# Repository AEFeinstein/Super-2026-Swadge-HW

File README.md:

# Super Magfest 2027 Swadge Hardware

## Welcome

This is the hardware repository for the Super Magfest 2027 Swadge.

The corresponding firmware repository for the Super Magfest 2027 Swadge [can be found here](https://github.com/AEFeinstein/Super-2024-Swadge-FW).

If you have any questions, feel free to create a Github ticket or email us at circuitboards@magfest.org.

## Render

Coming eventually!

## Schematic

Coming eventually!

## Directories

### `art`

This directory has the SVGs used to generate the KiCad files. The SVGs are drawn in [Inkscape](https://inkscape.org/).

### `Swadge-Parts`

This directory is a git submodule which has all the parts, footprints, and 3D models used in the KiCad project.

### `Swadge-HW`

This directory has the KiCad project for the main Swadge PCB.

### `Swadge-HW/3d Print`

This directory has the 3D print files for the 2026 Swadge.

### `Swadge-HW/Manufacturing Information`

This directory has information about manufacturing the Swdage PCB.

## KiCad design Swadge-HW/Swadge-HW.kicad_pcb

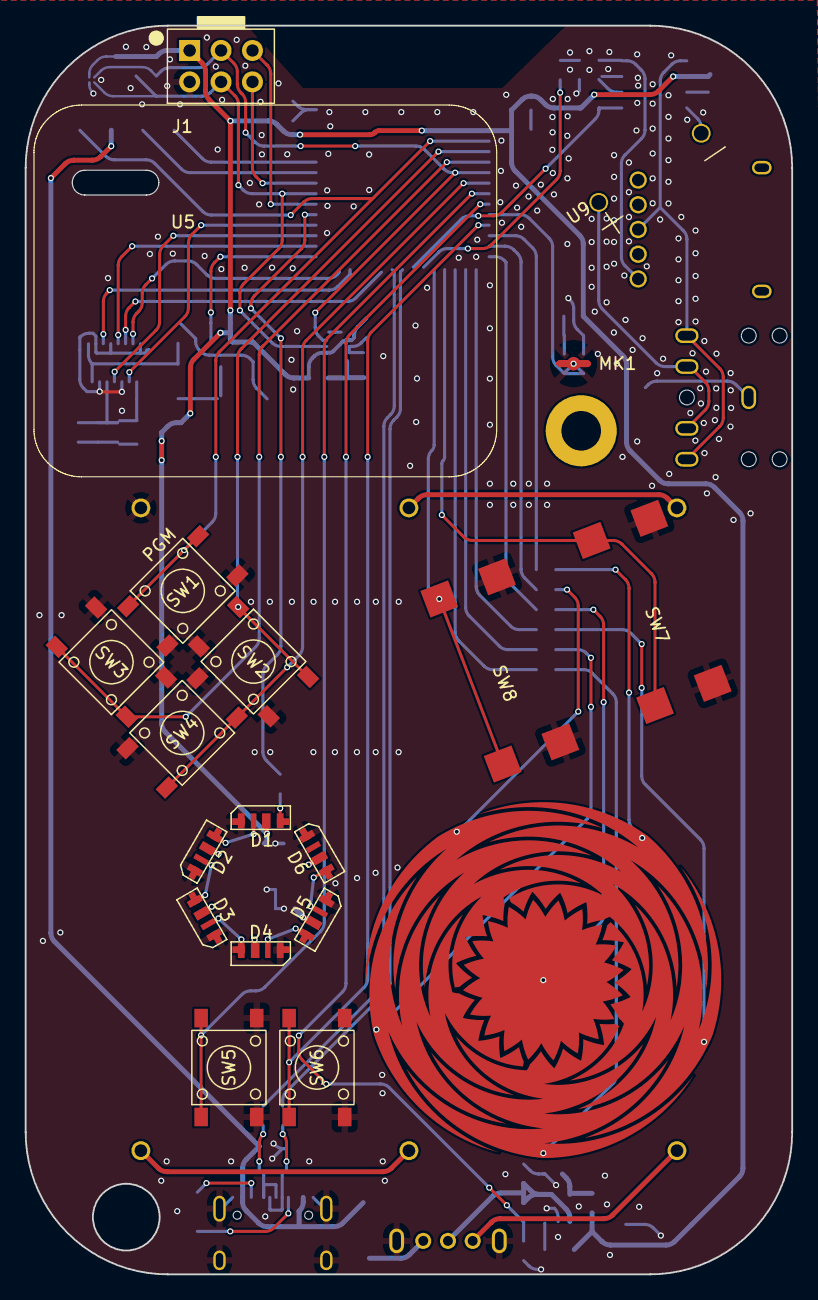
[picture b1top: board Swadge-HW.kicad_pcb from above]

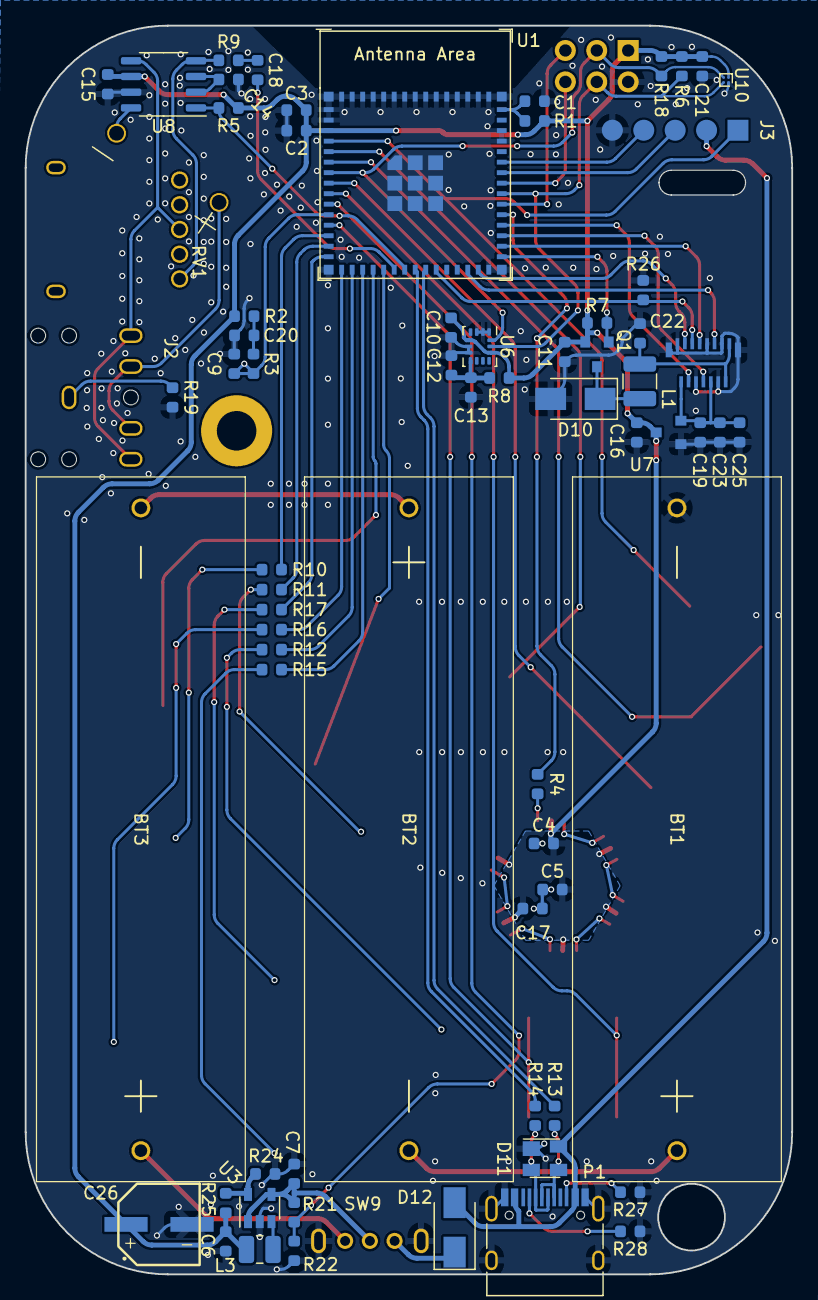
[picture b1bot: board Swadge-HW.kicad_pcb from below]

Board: 2 copper layers, 62.0 x 101.0 mm, 90 parts (70 on the bottom side), 73 nets.

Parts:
BT1, BT2, BT3: Battery; 2460
C1, C4, C5, C6, C7, C11, C14, C15, C17, C19: 1μF; C_0603_1608Metric
C2, C12, C20, C22: 22μF; C_0603_1608Metric
C3, C10, C13, C16, C23, C25: 0.1μF; C_0603_1608Metric
C9: 4.7nF; C_0603_1608Metric
C18: 0.39μF; C_0603_1608Metric
C21: 2.2μF; C_0603_1608Metric
C26: C_Polarized_US; C_Radial_D6.3_L5.8_P5.34
D1, D2, D3, D4, D5, D6: SK6812-SIDE-A; SK6812_SIDE_2
D10, D12: D; D_SMA
D11: SP0503BAHT; SOT-143
J1: Conn_02x03_Odd_Even; PinSocket_2x03_P2.54mm_Vertical
J2: PJ-307C
J3: Conn_01x05_Male; PinHeader_1x05_P2.54mm_Vertical
L1: 33uH_500mA; L_1210_3225Metric
L3: 2.2uH; L_1008_2520Metric
MK1: Microphone; INGHAi_MIC_GMI4013S-2C58DB
P1: USB_C_Plug_USB2.0; USB_C_Receptacle_HRO_TYPE-C-31-M-12
Q1: Q_PMOS_GSD; SOT-23
R1, R7, R22, R24, R26: 10kΩ; R_0603_1608Metric
R2, R4, R8, R13, R14: 33Ω; R_0603_1608Metric
R3: 12kΩ; R_0603_1608Metric
R5, R9: 20kΩ; R_0603_1608Metric
R6, R18, R27, R28: 5.1kΩ; R_0603_1608Metric
R10, R11, R12, R15, R16, R17: 510Ω; R_0603_1608Metric
R19: 120Ω; R_0603_1608Metric
R21, R25: 43kΩ; R_0603_1608Metric
RV1: R_Potentiometer_US_SMD; RK10J11E0034
SW1, SW2, SW3, SW4, SW5, SW6: YTS-D003-1A
SW7, SW8: TS-1103S-B-B; B3FS4002P
SW9: SW_SPDT_1825232-1; 1825232-1
U1: ESP32-S2-MINI-1
U2: RB017A1505A; NULL
U3: M3410; SOT-23-5
U4: Touchpad_6_80
U5: RB017A1505A_Connector; HCTL HC-FPC-03-10-15RLTAG-TUCKED
U6: LSM6DSL; LGA-14_3x2.5mm_P0.5mm_LayoutBorder3x4y
U7: GENERIC_LDO_GOI; SOT-23
U8: FM8002A; SOP-8_3.9x4.9mm_P1.27mm
U9: INGHAi_GSPK2307P-8R1W; INGHAi GSPK2308P-8R0.5W
U10: BGA-4-.83x.83

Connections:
3V3: C2.1, C3.1, C4.1, C5.1, C6.1, C10.1, C11.1, C15.1, C16.1, C17.1, C21.1, C26.1, D1.2 (VDD), D2.2 (VDD), D3.2 (VDD), D4.2 (VDD), D5.2 (VDD), D6.2 (VDD), J1.1, L3.1, Q1.2 (S), R1.1, R2.2, R5.1, R6.2, R7.1, R8.2, R18.1, R25.2, U1.3 (3V3), U6.5 (VDDIO), U6.12 (CS), U7.3 (IN), U8.6 (VDD), U10.B1 (VDD)
5VIN: D11.4 (K), D12.2 (A), J3.2, P1.A4_B9 (VBUS), P1.A9_B4 (VBUS)
+5V: D12.1 (K), SW9.3 (C)
BATTMID: BT1.1 (+), BT2.2 (-)
BATTMID2: BT2.1 (+), BT3.2 (-)
BATTPLUS: BT3.1 (+), SW9.1 (A)
BTN_1: J3.1, SW1.1, SW1.2, U1.4 (GPIO0/BOOT)
BTN_2: SW2.1, SW2.2, U1.5 (GPIO1/ADC1_CH0)
BTN_3: SW3.1, SW3.2, U1.6 (GPIO2/ADC1_CH1)
BTN_4: SW4.1, SW4.2, U1.8 (GPIO4/ADC1_CH3)
BTN_5: SW5.1, SW5.2, U1.9 (GPIO5/ADC1_CH4)
BTN_6: SW6.1, SW6.2, U1.12 (GPIO8/ADC1_CH7)
BTN_7: SW7.1 (COM_1), SW7.2 (COM_2), U1.19 (GPIO15/ADC2_CH4/XTAL_32K_P)
BTN_8: SW8.1 (COM_1), SW8.2 (COM_2), U1.20 (GPIO16/ADC2_CH5/XTAL_32K_N)
CC1: P1.A5 (CC1), R28.2
CC2: P1.B5 (CC2), R27.2
EN: C1.1, R1.2, U1.45 (CHIP/PU/RESET)
GND: BT1.2 (-), C1.2, C2.2, C3.2, C4.2, C5.2, C6.2, C7.2, C9.1, C10.2, C11.2, C12.2, C13.2, C14.1, C15.2, C16.2, C17.2, C19.2, C20.2, C21.2, C22.2, C23.2, C25.2, C26.2, D1.4 (GND), D2.4 (GND), D3.4 (GND), D4.4 (GND), D5.4 (GND), D6.4 (GND), D10.2 (A), D11.1 (A), J1.2, J3.5, MK1.1 (-), P1.A1_B12 (GND), P1.A12_B1 (GND), P1.S1 (SHIELD), R19.1, R22.2, R24.1, R26.2, R27.1, R28.1, SW1.3, SW1.4, SW2.3, SW2.4, SW3.3, SW3.4, SW4.3, SW4.4, SW5.3, SW5.4, SW6.3, SW6.4, SW7.3 (NO_1), SW7.4 (NO_2), SW8.3 (NO_1), SW8.4 (NO_2), SW9.4 (D), SW9.5 (E), U1.1 (GND), U1.2 (GND), U1.30 (GND), U1.42 (GND), U1.43 (GND), U1.46 (GND), U1.47 (GND), U1.48 (GND), U1.49 (GND), U1.50 (GND), U1.51 (GND), U1.52 (GND), U1.53 (GND), U1.54 (GND), U1.55 (GND), U1.56 (GND), U1.57 (GND), U1.58 (GND), U1.59 (GND), U1.60 (GND), U1.61 (GND), U1.62 (GND), U1.63 (GND), U1.64 (GND), U1.65 (GND), U3.2 (GND), U5.1 (GND), U5.6 (GND), U5.9 (GND), U5.12 (LED-), U5.13 (LED-), U5.16 (GND), U5.17 (GND), U6.1 (SA0), U6.2 (SDx), U6.3 (SCx), U6.6 (GND), U6.7 (GND), U7.1 (GND), U8.7 (GND), U10.A1 (VSS)
GPIO40: J1.5, U1.36 (MTDO/JTAG/GPIO40)
GPIO42: J1.6, U1.38 (MTMS/JTAG/GPIO42)
LCD28: C19.1, C23.1, C25.1, U5.2 (VCC1.8V), U5.10 (VDD2.8V), U7.2 (OUT)
LED: R4.2, U1.35 (MTCK/JTAG/GPIO39)
MIC: C9.2, MK1.2 (+), R3.2, U1.11 (GPIO7/ADC1_CH6)
unnamed: C18.1, R9.1
unnamed: C20.1, R2.1, R3.1
unnamed: D1.1 (IN), R4.1
unnamed: D1.3 (OUT), D2.1 (IN)
unnamed: D2.3 (OUT), D3.1 (IN)
unnamed: D3.3 (OUT), D4.1 (IN)
unnamed: D4.3 (OUT), D5.1 (IN)
unnamed: D5.3 (OUT), D6.1 (IN)
unnamed: D10.1 (K), L1.1, Q1.3 (D)
unnamed: J2.1, R19.2
unnamed: D11.2 (K), P1.A7 (DN1), P1.B7 (DN2), R14.2
unnamed: D11.3 (K), P1.A6 (DP1), P1.B6 (DP2), R13.2
unnamed: R24.2, R25.1, U3.5 (FB)
unnamed: L3.2, U3.3 (LX)
unnamed: R10.2, U4.1 (Bottom)
unnamed: R17.2, U4.6 (Center)
unnamed: R16.2, U4.5 (Left)
unnamed: R11.2, U4.2 (Right)
unnamed: R15.2, U4.4 (Top_Left)
unnamed: R12.2, U4.3 (Top_Right)
unnamed: C12.1, C13.1, R8.1, U6.8 (VDD)
unnamed: C14.2, U8.2 (Bypass), U8.3 (IN+)
unnamed: R9.2, RV1.1, U8.4 (IN-)
unnamed: J2.2, J2.5, RV1.2, U8.5 (VO1)
unnamed: U8.8 (VO2), U9.2 (-)
unnamed: J2.3, J2.4, U9.1 (+)
RX: J3.4, U1.40 (GPIO44/U0RXD/PROG)
SCL: J1.4, R6.1, U1.37 (MTDI/JTAG/GPIO41), U6.13 (SCL), U10.A2 (SCL)
SDA: J1.3, R18.2, U1.7 (GPIO3/ADC1_CH2), U6.14 (SDA), U10.B2 (SDA)
SNODE: C7.1, R21.2, SW9.2 (B), U3.1 (EN), U3.4 (VIN)
SPK: C18.2, U1.21 (ADC2_CH7/DAC_2/GPIO17)
SPK_SHDN: R5.2, U1.22 (ADC2_CH6/DAC_1/GPIO18), U8.1 (Shutdown)
TFTATP: Q1.1 (G), R7.2, U1.31 (GPIO35)
TFT_CS: U1.29 (GPIO34), U5.3 (CS)
TFT_FMARK: U1.28 (GPIO33), U5.11 (FMARK)
TFT_LEDA: C22.1, L1.2, U5.14 (LED+), U5.15 (LED+)
TFT_RESET: U1.34 (GPIO38), U5.4 (RESET)
TFT_RS: R26.1, U1.25 (GPIO21), U5.5 (RS)
TFT_SCL: U1.32 (GPIO36), U5.7 (SCL)
TFT_SDA: U1.33 (GPIO37), U5.8 (SDA)
TOUCH_1: R10.1, U1.13 (GPIO9/ADC1_CH8)
TOUCH_2: R11.1, U1.14 (GPIO10/ADC1_CH9)
TOUCH_3: R17.1, U1.15 (GPIO11/ADC2_CH0)
TOUCH_4: R16.1, U1.16 (GPIO12/ADC2_CH1)
TOUCH_5: R12.1, U1.17 (GPIO13/ADC2_CH2)
TOUCH_6: R15.1, U1.18 (GPIO14/ADC2_CH3)
TX: J3.3, U1.39 (GPIO43/U0TXD/PROG)
USB_D+: R13.1, U1.24 (USB_D+/ADC2_CH9/GPIO20)
USB_D-: R14.1, U1.23 (USB_D-/ADC2_CH8/GPIO19)
VMON: R21.1, R22.1, U1.10 (GPIO6/ADC1_CH5)

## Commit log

2024-05-04 Rename Gunship to Hotdog
2024-07-21 Replace buzzer with speaker Clean up schematic
2024-07-21 Add LCSC part numbers, costs
2024-07-21 Reset PCB
2024-07-21 #1 Add ESD resistors to touchpads
2024-07-21 Added volume potentiometer
2024-07-22 Put touchpad on board
2024-07-23 Add idea of a shape and layout
2024-07-29 Added art source
2024-07-30 Added acrylic sausage, SMD pot
2024-08-09 Added art files
2024-08-09 Updated to new board shape
2024-08-10 Placed big parts
2024-08-10 Added condiment part
2024-08-14 Layout v0.5
    Placement of 80% of SMD components
    Add QMC6309
    DNP D9
    Move Power Switch to right dog
    Bump Aux port over
2024-08-14 Update Swadge-Parts
2024-08-15 Layout 0.6
    still tweaking
2024-08-16 Layout 0.7
    Is endless screaming an option for a description?
    10lbs of swadge in a 5lb layout. Moved some USB peripherals after plagiarizing from the gunship layout, more attempts to work myself out of the corner of my own creation. Need to consider moving all 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
2024-08-19 Layout 0.9
    for review
2024-08-20 Fix DRC things
2024-08-29 update from changes made by charlesl pre-order
2024-09-02 Update to order for rev - before checking footprint on ESP32-S2
2024-09-02 After updating footprint
2024-09-09 PCB outline and acrylic adjustments
    Adjusted SVGs to grow PCB and add acrylic bun. TODO: update in kicad
2024-09-18 Increase board size and add new acrylic
    grew pcb, added bun outline, nudged some components
2024-09-19 Modify silk art and minor layout adjustments
    Bump screen to right, bump switch inside, update silk art, nudge LED for clearance concerns
2024-09-23 Update silkscreen
2024-09-23 Add PGM to silkscreen
2024-09-23 Route USB & power switch circuitry
2024-09-24 Lots of routing
2024-09-24 Fully route
2024-09-26 Cleanup routing
2024-09-26 Fix PGM silkscreen
2024-09-26 Add Comic Sans
2024-09-26 Added teardrops
2024-09-26 More filleting, promise I'm done smoothing things
2024-09-30 Pull passives back from edge
2024-10-01 Emerald touchpad, adjust characters
2024-10-03 Add electrolytic capacitor C26
    add capacitor for noise management
2024-10-07 Generate RB manufacturing data, small edits
    Change footprint for C26 + BOM Data
    Add notch in Acrylic for fitment
    Update schematic to reflect C26 change
    Add quote data
    Update condiment dxf/svg
2024-10-07 Update mfg files
    Updated mfg files for elecrow quote
2024-10-09 Mostly art and silk updates
    add garbotnik
    edit silk
    add touchpad label
    update condiment step
2024-10-10 quoting data to prepare for order
2024-10-10 fix short on garbotnik, schematic parity
    C26 pointed at different part on schematic
    garbotnik was shorted to ground
2024-10-11 Rev 0 for release
2024-10-14 final_updated_final_no_this_one
    DNP U10, C21
    Fixing my dyslexia in the quote information
2024-10-21 Rev 1.1
    add R19
2024-11-21 Silk rev D
    Add screen outline
2025-02-02 Paperwork makes the dream work
    Schematic, render, readme updates
2025-02-02 3D files
2025-02-02 Schematic upload
2025-03-29 Clean out last year's files (PCB, Art, Shell) Update READMEs
2025-06-08 Add LED matrix and CH32v003 Repopulate magnometer and associated components DNP giant capacitor Change sheet size to 11x17 Change labels to 2026
2025-06-25 preliminary layout
    placed most of the important bits
2025-06-26 Half the routing done
    Do you think God stays in heaven because he, too, lives in fear of what he's created here on earth?
2025-07-03 ROUTED
    proto A
2025-07-09 fixing some routing problems
    haven't resolved DRC just yet. someday i will learn how github works
2025-07-11 Rearrange LEDs, buttons. Fix DRC
2025-07-11 Fixed DRC errors and Added Thermal Reliefs
    Added some thermal relief to parts. Fixed Some DRC errors.
    Now there are 0 DRC errors.
2025-07-11 Added A Relief Hole
    Like the title says. i added a "relief" hole, mainly to allow people to hang it up via a Lanyard or something
2025-07-11 Tell git to ignore Mac specific files
    Tell git to ignore Mac specific files
2025-07-12 art and fonts
2025-07-15 Create rev A shape, routing
    Replaced screen footprint with variant that tucks ribbon
    scale touchpad to 80%
    add R35 5.1k pullup on GPIO42 for CH32v003
    DNP D7-D9 + caps
2025-07-18 corrected a bunch of DRC errors, did some of the work that was suggested on Slack and improved the fill by manipulating some of the tracks and Via’s.
2025-07-18 Update Swadge-HW.kicad_pro
    update Pt2
2025-07-18 Added missing part to lib, fixed DRC warnings, updated submodule
2025-08-26 Fixing footprint errors on Ls and SAO
    Associated with
    https://github.com/AEFeinstein/Super-2026-Swadge-HW/issues/9
2025-08-28 What am I even doing
2025-08-28 Oops wrong branch
2025-08-28 Make it small
2025-08-28 Why am I routing this?
2025-08-29 Fully routed
2025-09-01 Routing fun
2025-09-03 BOM adjustments and unrouting for rev B
    fixing problems from issues #7 #8 #9 #10
2025-09-03 Fixing LED array pinout
    adjusting pinout to ch32v003 to match the SAO pinout. flipped LEDs 180deg in schematic. please check my work I am so nervous about this
2025-09-03 reroute rev B
    Rerouted with updates to sch and footprints
2025-09-04 Adjust netclasses, warnings
2025-09-04 BOM adjustments for production
2025-09-04 Smooth head, add holes to acrylic
2025-09-04 Properly orient SAO
2025-09-04 Thicken power traces
2025-09-04 DRC Warning fix
2025-09-04 Sprinkle vias
2025-09-04 Remove stray hole
2025-09-05 Fillet tracks, fix SAO, vias
2025-09-05 Fixed the screen 3D Model, now its centered on the footprint and the cable wraps around and connects to the bottom.
2025-09-06 Fix button order
2025-09-06 Fixed button placement
2025-09-08 add mounting holes, bump buttons
2025-09-08 reroute touchpad
2025-09-08 Dismantled a couple minor DRC errors and Wacked a few Warnings. Tee’d up some Thermal relief via’s to a few of the pins (overkill honestly).
2025-09-09 Update touchpad
2025-09-09 Silkscreen integration and cleanup
    SAO part fix, pin variant was selected not header
    integrate greg's silkscreen design
    cleanup refdes all over the board
    add version, circuitboards, website on back
    touchpad is still yelling about polygons but at this point i don't really care
2025-09-10 Use relative paths
2025-09-10 Show correct LED models
2025-09-10 Fixed CH32V003 model
2025-09-10 Added preliminary folded ribbon screen model
2025-09-10 manufacturing files
2025-09-17 bump to v1.1
    replace RV1 with available component
2025-09-22 Update Swadge-HW.kicad_pcb
    move pot mark to fab layer, was improperly marked as silk
2025-10-06 V1.2
    per dacs request
    1. shrink touchpad
    2. move batteries
    3. move R10 and R11
    4. delete/move mounting holes
2025-10-06 Update Swadge-HW.kicad_pcb
    Move power button
2025-10-06 Fix DRC
2025-10-14 mfg files
2025-10-28 DNP the eye LEDs and board outline
2025-10-28 Sync PCB with SCH
2025-11-02 Fix LCSC parts
2025-11-03 Exclude parts from BOM
2025-11-03 Replace tactile switch
2025-11-03 Replace SAO pins with socket
2025-11-03 Exclude J3 from BOM, Add LCSC for AA holders
2025-11-03 Update inductor LCSC
2025-11-10 Squeeze batteries, add mounting hole, add vias
2025-11-11 Add art
2025-11-11 Rotate IMU
2025-11-11 Add gear art, signature Remove silk from top Add more vias Populate C26, 3D model
2025-11-11 Adjust TFT for fabrication
2025-11-12 Sync SCH and PCB
2025-11-13 Adjust part placement for JLC manufacturing
2025-11-13 Fix 3D model placement
2025-11-19 Fix 3D part rotation
2025-11-20 Update Swadge-HW.kicad_pcb
    outline fix for v1.2
2025-11-24 Fix silkscreen
2025-11-24 Adjust TFT silkscreen
2025-12-23 Uploaded Swadge Add-on STEP files
    Added Shell Prototype file, Diffuser addon plus template design, as well as alternate Printable diffuser crest.
2025-12-31 Update README.MD
    Added descriptions about add-ons and assmebly
2026-01-19 Update README.MD
    Added description about Visor and Slicer program used
2026-01-19 Added Orcaslicer compatible 3MF files
2026-04-04 Revert "initial commit"
    This reverts commit 0464ea491c95b659d104dd14c666d512c40c896c.
2026-05-28 uploading some loose ends
    IM file, silk
